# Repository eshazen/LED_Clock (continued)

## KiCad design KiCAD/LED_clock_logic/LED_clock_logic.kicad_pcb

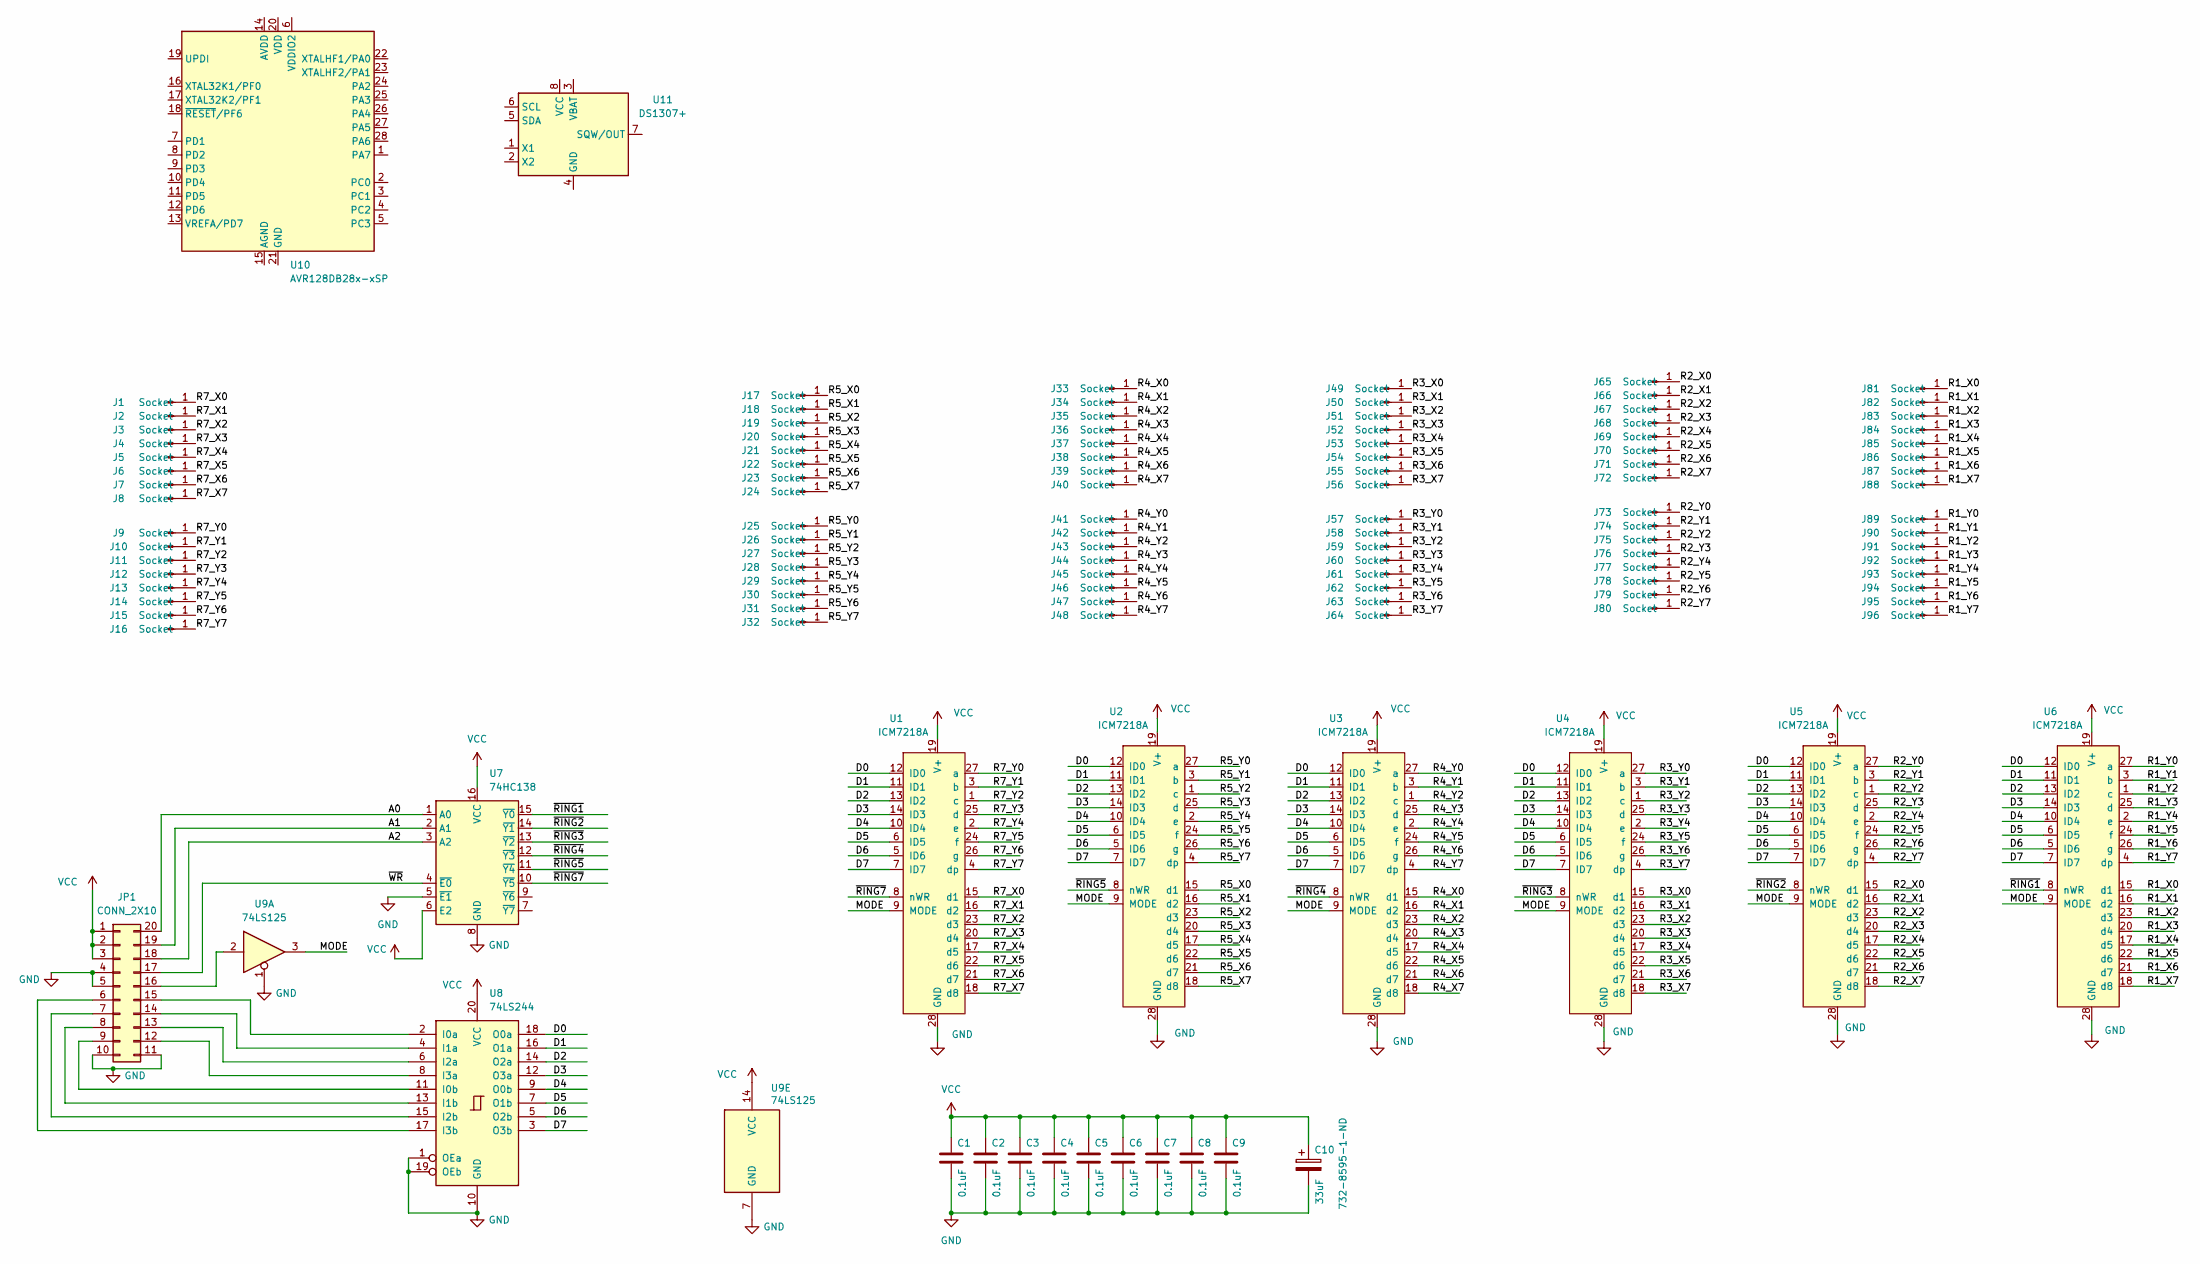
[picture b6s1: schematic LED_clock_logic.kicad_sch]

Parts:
C1, C2, C3, C4, C5, C6, C7, C8, C9: 0.1uF; C_Disc_D4.3mm_W1.9mm_P5.00mm
C10: 33uF; CP_Radial_D5.0mm_P2.00mm
J1, J2, J3, J4, J5, J6, J7, J8, J9, J10, J11, J12, J13, J14, J15, J16, J17, J18, J19, J20, J21, J22, J23, J24, J25, J26, J27, J28, J29, J30, J31, J32, J33, J34, J35, J36, J37, J38, J39, J40, J41, J42, J43, J44, J45, J46, J47, J48, J49, J50, J51, J52, J53, J54, J55, J56, J57, J58, J59, J60, J61, J62, J63, J64, J65, J66, J67, J68, J69, J70, J71, J72, J73, J74, J75, J76, J77, J78, J79, J80, J81, J82, J83, J84, J85, J86, J87, J88, J89, J90, J91, J92, J93, J94, J95, J96: Socket; TestPoint_THTPad_D2.0mm_Drill1.0mm
JP1: CONN_2X10; PinHeader_2x10_P2.54mm_Vertical
U1, U2, U3, U4, U5, U6: ICM7218A; DIP-28_W15.24mm_LongPads
U7: 74HC138; DIP-16_W7.62mm_LongPads
U8: 74LS244; DIP-20_W7.62mm_LongPads
U9: 74LS125; DIP-14_W7.62mm_LongPads
U10: AVR128DB28x-xSP; DIP-28_W7.62mm
U11: DS1307+; DIP-8_W7.62mm

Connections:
/A0: JP1.20, U7.1 (A0)
/A1: JP1.19, U7.2 (A1)
/A2: JP1.18, U7.3 (A2)
/D0: U1.12 (ID0), U2.12 (ID0), U3.12 (ID0), U4.12 (ID0), U5.12 (ID0), U6.12 (ID0), U8.18 (O0a)
/D1: U1.11 (ID1), U2.11 (ID1), U3.11 (ID1), U4.11 (ID1), U5.11 (ID1), U6.11 (ID1), U8.16 (O1a)
/D2: U1.13 (ID2), U2.13 (ID2), U3.13 (ID2), U4.13 (ID2), U5.13 (ID2), U6.13 (ID2), U8.14 (O2a)
/D3: U1.14 (ID3), U2.14 (ID3), U3.14 (ID3), U4.14 (ID3), U5.14 (ID3), U6.14 (ID3), U8.12 (O3a)
/D4: U1.10 (ID4), U2.10 (ID4), U3.10 (ID4), U4.10 (ID4), U5.10 (ID4), U6.10 (ID4), U8.9 (O0b)
/D5: U1.6 (ID5), U2.6 (ID5), U3.6 (ID5), U4.6 (ID5), U5.6 (ID5), U6.6 (ID5), U8.7 (O1b)
/D6: U1.5 (ID6), U2.5 (ID6), U3.5 (ID6), U4.5 (ID6), U5.5 (ID6), U6.5 (ID6), U8.5 (O2b)
/D7: U1.7 (ID7), U2.7 (ID7), U3.7 (ID7), U4.7 (ID7), U5.7 (ID7), U6.7 (ID7), U8.3 (O3b)
/MODE: U1.9 (MODE), U2.9 (MODE), U3.9 (MODE), U4.9 (MODE), U5.9 (MODE), U6.9 (MODE), U9.3
/R1_X0: J81.1, U6.15 (d1)
/R1_X1: J82.1, U6.16 (d2)
/R1_X2: J83.1, U6.23 (d3)
/R1_X3: J84.1, U6.20 (d4)
/R1_X4: J85.1, U6.17 (d5)
/R1_X5: J86.1, U6.22 (d6)
/R1_X6: J87.1, U6.21 (d7)
/R1_X7: J88.1, U6.18 (d8)
/R1_Y0: J89.1, U6.27 (a)
/R1_Y1: J90.1, U6.3 (b)
/R1_Y2: J91.1, U6.1 (c)
/R1_Y3: J92.1, U6.25 (d)
/R1_Y4: J93.1, U6.2 (e)
/R1_Y5: J94.1, U6.24 (f)
/R1_Y6: J95.1, U6.26 (g)
/R1_Y7: J96.1, U6.4 (dp)
/R2_X0: J65.1, U5.15 (d1)
/R2_X1: J66.1, U5.16 (d2)
/R2_X2: J67.1, U5.23 (d3)
/R2_X3: J68.1, U5.20 (d4)
/R2_X4: J69.1, U5.17 (d5)
/R2_X5: J70.1, U5.22 (d6)
/R2_X6: J71.1, U5.21 (d7)
/R2_X7: J72.1, U5.18 (d8)
/R2_Y0: J73.1, U5.27 (a)
/R2_Y1: J74.1, U5.3 (b)
/R2_Y2: J75.1, U5.1 (c)
/R2_Y3: J76.1, U5.25 (d)
/R2_Y4: J77.1, U5.2 (e)
/R2_Y5: J78.1, U5.24 (f)
/R2_Y6: J79.1, U5.26 (g)
/R2_Y7: J80.1, U5.4 (dp)
/R3_X0: J49.1, U4.15 (d1)
/R3_X1: J50.1, U4.16 (d2)
/R3_X2: J51.1, U4.23 (d3)
/R3_X3: J52.1, U4.20 (d4)
/R3_X4: J53.1, U4.17 (d5)
/R3_X5: J54.1, U4.22 (d6)
/R3_X6: J55.1, U4.21 (d7)
/R3_X7: J56.1, U4.18 (d8)
/R3_Y0: J57.1, U4.27 (a)
/R3_Y1: J58.1, U4.3 (b)
/R3_Y2: J59.1, U4.1 (c)
/R3_Y3: J60.1, U4.25 (d)
/R3_Y4: J61.1, U4.2 (e)
/R3_Y5: J62.1, U4.24 (f)
/R3_Y6: J63.1, U4.26 (g)
/R3_Y7: J64.1, U4.4 (dp)
/R4_X0: J33.1, U3.15 (d1)
/R4_X1: J34.1, U3.16 (d2)
/R4_X2: J35.1, U3.23 (d3)
/R4_X3: J36.1, U3.20 (d4)
/R4_X4: J37.1, U3.17 (d5)
/R4_X5: J38.1, U3.22 (d6)
/R4_X6: J39.1, U3.21 (d7)
/R4_X7: J40.1, U3.18 (d8)
/R4_Y0: J41.1, U3.27 (a)
/R4_Y1: J42.1, U3.3 (b)
/R4_Y2: J43.1, U3.1 (c)
/R4_Y3: J44.1, U3.25 (d)
/R4_Y4: J45.1, U3.2 (e)
/R4_Y5: J46.1, U3.24 (f)
/R4_Y6: J47.1, U3.26 (g)
/R4_Y7: J48.1, U3.4 (dp)
/R5_X0: J17.1, U2.15 (d1)
/R5_X1: J18.1, U2.16 (d2)
/R5_X2: J19.1, U2.23 (d3)
/R5_X3: J20.1, U2.20 (d4)
/R5_X4: J21.1, U2.17 (d5)
/R5_X5: J22.1, U2.22 (d6)
/R5_X6: J23.1, U2.21 (d7)
/R5_X7: J24.1, U2.18 (d8)
/R5_Y0: J25.1, U2.27 (a)
/R5_Y1: J26.1, U2.3 (b)
/R5_Y2: J27.1, U2.1 (c)
/R5_Y3: J28.1, U2.25 (d)
/R5_Y4: J29.1, U2.2 (e)
/R5_Y5: J30.1, U2.24 (f)
/R5_Y6: J31.1, U2.26 (g)
/R5_Y7: J32.1, U2.4 (dp)
/R7_X0: J1.1, U1.15 (d1)
/R7_X1: J2.1, U1.16 (d2)
/R7_X2: J3.1, U1.23 (d3)
/R7_X3: J4.1, U1.20 (d4)
/R7_X4: J5.1, U1.17 (d5)
/R7_X5: J6.1, U1.22 (d6)
/R7_X6: J7.1, U1.21 (d7)
/R7_X7: J8.1, U1.18 (d8)
/R7_Y0: J9.1, U1.27 (a)
/R7_Y1: J10.1, U1.3 (b)
/R7_Y2: J11.1, U1.1 (c)
/R7_Y3: J12.1, U1.25 (d)
/R7_Y4: J13.1, U1.2 (e)
/R7_Y5: J14.1, U1.24 (f)
/R7_Y6: J15.1, U1.26 (g)
/R7_Y7: J16.1, U1.4 (dp)
/~RING1: U6.8 (nWR), U7.15 (~Y0)
/~RING2: U5.8 (nWR), U7.14 (~Y1)
/~RING3: U4.8 (nWR), U7.13 (~Y2)
/~RING4: U3.8 (nWR), U7.12 (~Y3)
/~RING5: U2.8 (nWR), U7.11 (~Y4)
/~RING7: U1.8 (nWR), U7.10 (~Y5)
/~WR: JP1.17, U7.4 (~E0)
GND: C1.2, C2.2, C3.2, C4.2, C5.2, C6.2, C7.2, C8.2, C9.2, C10.2, JP1.4, JP1.5, JP1.10, JP1.11, U1.28 (GND), U2.28 (GND), U3.28 (GND), U4.28 (GND), U5.28 (GND), U6.28 (GND), U7.5 (~E1), U7.8 (GND), U8.1 (OEa), U8.10 (GND), U8.19 (OEb), U9.1, U9.7 (GND)
unnamed: JP1.6, U8.17 (I3b)
unnamed: JP1.7, U8.15 (I2b)
unnamed: JP1.8, U8.13 (I1b)
unnamed: JP1.9, U8.11 (I0b)
unnamed: JP1.12, U8.8 (I3a)
unnamed: JP1.13, U8.6 (I2a)
unnamed: JP1.14, U8.4 (I1a)
unnamed: JP1.15, U8.2 (I0a)
unnamed: JP1.16, U9.2
VCC: C1.1, C2.1, C3.1, C4.1, C5.1, C6.1, C7.1, C8.1, C9.1, C10.1, JP1.1, JP1.2, JP1.3, U1.19 (V+), U2.19 (V+), U3.19 (V+), U4.19 (V+), U5.19 (V+), U6.19 (V+), U7.6 (E2), U7.16 (VCC), U8.20 (VCC), U9.14 (VCC)

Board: 2 copper layers, 118 parts (0 on the bottom side), 126 nets, no tracks yet.

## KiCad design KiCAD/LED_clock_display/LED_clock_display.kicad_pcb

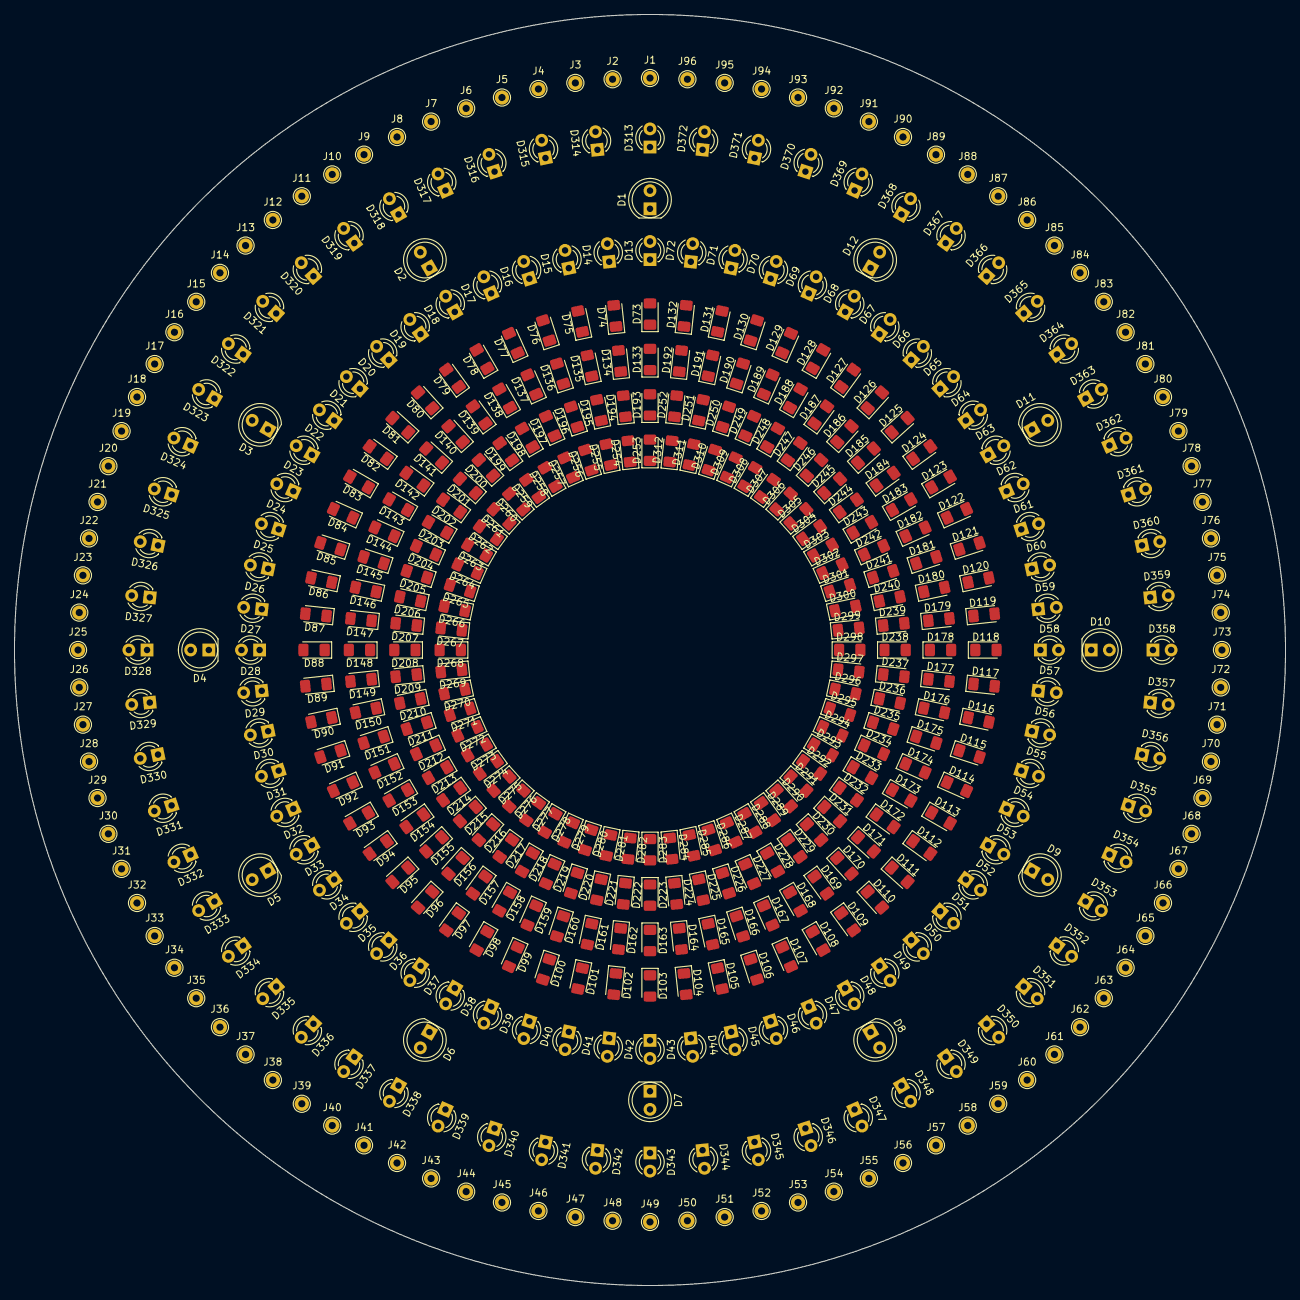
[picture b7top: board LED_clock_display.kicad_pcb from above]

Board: 2 copper layers, 177.8 x 177.8 mm, 468 parts (0 on the bottom side), 96 nets, no tracks yet.

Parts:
D1, D2, D3, D4, D5, D6, D7, D8, D9, D10, D11, D12: LED; LED_D5.0mm
D13, D14, D15, D16, D17, D18, D19, D20, D21, D22, D23, D24, D25, D26, D27, D28, D29, D30, D31, D32, D33, D34, D35, D36, D37, D38, D39, D40, D41, D42, D43, D44, D45, D46, D47, D48, D49, D50, D51, D52, D53, D54, D55, D56, D57, D58, D59, D60, D61, D62, D63, D64, D65, D66, D67, D68, D69, D70, D71, D72, D313, D314, D315, D316, D317, D318, D319, D320, D321, D322, D323, D324, D325, D326, D327, D328, D329, D330, D331, D332, D333, D334, D335, D336, D337, D338, D339, D340, D341, D342, D343, D344, D345, D346, D347, D348, D349, D350, D351, D352, D353, D354, D355, D356, D357, D358, D359, D360, D361, D362, D363, D364, D365, D366, D367, D368, D369, D370, D371, D372: LED; LED_D3.0mm
D73, D74, D75, D76, D77, D78, D79, D80, D81, D82, D83, D84, D85, D86, D87, D88, D89, D90, D91, D92, D93, D94, D95, D96, D97, D98, D99, D100, D101, D102, D103, D104, D105, D106, D107, D108, D109, D110, D111, D112, D113, D114, D115, D116, D117, D118, D119, D120, D121, D122, D123, D124, D125, D126, D127, D128, D129, D130, D131, D132, D133, D134, D135, D136, D137, D138, D139, D140, D141, D142, D143, D144, D145, D146, D147, D148, D149, D150, D151, D152, D153, D154, D155, D156, D157, D158, D159, D160, D161, D162, D163, D164, D165, D166, D167, D168, D169, D170, D171, D172, D173, D174, D175, D176, D177, D178, D179, D180, D181, D182, D183, D184, D185, D186, D187, D188, D189, D190, D191, D192, D193, D194, D195, D196, D197, D198, D199, D200, D201, D202, D203, D204, D205, D206, D207, D208, D209, D210, D211, D212, D213, D214, D215, D216, D217, D218, D219, D220, D221, D222, D223, D224, D225, D226, D227, D228, D229, D230, D231, D232, D233, D234, D235, D236, D237, D238, D239, D240, D241, D242, D243, D244, D245, D246, D247, D248, D249, D250, D251, D252, D253, D254, D255, D256, D257, D258, D259, D260, D261, D262, D263, D264, D265, D266, D267, D268, D269, D270, D271, D272, D273, D274, D275, D276, D277, D278, D279, D280, D281, D282, D283, D284, D285, D286, D287, D288, D289, D290, D291, D292, D293, D294, D295, D296, D297, D298, D299, D300, D301, D302, D303, D304, D305, D306, D307, D308, D309, D310, D311, D312: LED; LED_1206_3216Metric_Pad1.42x1.75mm_HandSolder
J1, J2, J3, J4, J5, J6, J7, J8, J9, J10, J11, J12, J13, J14, J15, J16, J17, J18, J19, J20, J21, J22, J23, J24, J25, J26, J27, J28, J29, J30, J31, J32, J33, J34, J35, J36, J37, J38, J39, J40, J41, J42, J43, J44, J45, J46, J47, J48, J49, J50, J51, J52, J53, J54, J55, J56, J57, J58, J59, J60, J61, J62, J63, J64, J65, J66, J67, J68, J69, J70, J71, J72, J73, J74, J75, J76, J77, J78, J79, J80, J81, J82, J83, J84, J85, J86, J87, J88, J89, J90, J91, J92, J93, J94, J95, J96: PIN; TestPoint_THTPad_D2.0mm_Drill1.0mm

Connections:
/R1_X0: D253.2 (A), D261.2 (A), D269.2 (A), D277.2 (A), D285.2 (A), D293.2 (A), D301.2 (A), D309.2 (A), J81.1
/R1_X1: D254.2 (A), D262.2 (A), D270.2 (A), D278.2 (A), D286.2 (A), D294.2 (A), D302.2 (A), D310.2 (A), J82.1
/R1_X2: D255.2 (A), D263.2 (A), D271.2 (A), D279.2 (A), D287.2 (A), D295.2 (A), D303.2 (A), D311.2 (A), J83.1
/R1_X3: D256.2 (A), D264.2 (A), D272.2 (A), D280.2 (A), D288.2 (A), D296.2 (A), D304.2 (A), D312.2 (A), J84.1
/R1_X4: D257.2 (A), D265.2 (A), D273.2 (A), D281.2 (A), D289.2 (A), D297.2 (A), D305.2 (A), J85.1
/R1_X5: D258.2 (A), D266.2 (A), D274.2 (A), D282.2 (A), D290.2 (A), D298.2 (A), D306.2 (A), J86.1
/R1_X6: D259.2 (A), D267.2 (A), D275.2 (A), D283.2 (A), D291.2 (A), D299.2 (A), D307.2 (A), J87.1
/R1_X7: D260.2 (A), D268.2 (A), D276.2 (A), D284.2 (A), D292.2 (A), D300.2 (A), D308.2 (A), J88.1
/R1_Y0: D253.1 (K), D254.1 (K), D255.1 (K), D256.1 (K), D257.1 (K), D258.1 (K), D259.1 (K), D260.1 (K), J89.1
/R1_Y1: D261.1 (K), D262.1 (K), D263.1 (K), D264.1 (K), D265.1 (K), D266.1 (K), D267.1 (K), D268.1 (K), J90.1
/R1_Y2: D269.1 (K), D270.1 (K), D271.1 (K), D272.1 (K), D273.1 (K), D274.1 (K), D275.1 (K), D276.1 (K), J91.1
/R1_Y3: D277.1 (K), D278.1 (K), D279.1 (K), D280.1 (K), D281.1 (K), D282.1 (K), D283.1 (K), D284.1 (K), J92.1
/R1_Y4: D285.1 (K), D286.1 (K), D287.1 (K), D288.1 (K), D289.1 (K), D290.1 (K), D291.1 (K), D292.1 (K), J93.1
/R1_Y5: D293.1 (K), D294.1 (K), D295.1 (K), D296.1 (K), D297.1 (K), D298.1 (K), D299.1 (K), D300.1 (K), J94.1
/R1_Y6: D301.1 (K), D302.1 (K), D303.1 (K), D304.1 (K), D305.1 (K), D306.1 (K), D307.1 (K), D308.1 (K), J95.1
/R1_Y7: D309.1 (K), D310.1 (K), D311.1 (K), D312.1 (K), J96.1
/R2_X0: D193.2 (A), D201.2 (A), D209.2 (A), D217.2 (A), D225.2 (A), D233.2 (A), D241.2 (A), D249.2 (A), J65.1
/R2_X1: D194.2 (A), D202.2 (A), D210.2 (A), D218.2 (A), D226.2 (A), D234.2 (A), D242.2 (A), D250.2 (A), J66.1
/R2_X2: D195.2 (A), D203.2 (A), D211.2 (A), D219.2 (A), D227.2 (A), D235.2 (A), D243.2 (A), D251.2 (A), J67.1
/R2_X3: D196.2 (A), D204.2 (A), D212.2 (A), D220.2 (A), D228.2 (A), D236.2 (A), D244.2 (A), D252.2 (A), J68.1
/R2_X4: D197.2 (A), D205.2 (A), D213.2 (A), D221.2 (A), D229.2 (A), D237.2 (A), D245.2 (A), J69.1
/R2_X5: D198.2 (A), D206.2 (A), D214.2 (A), D222.2 (A), D230.2 (A), D238.2 (A), D246.2 (A), J70.1
/R2_X6: D199.2 (A), D207.2 (A), D215.2 (A), D223.2 (A), D231.2 (A), D239.2 (A), D247.2 (A), J71.1
/R2_X7: D200.2 (A), D208.2 (A), D216.2 (A), D224.2 (A), D232.2 (A), D240.2 (A), D248.2 (A), J72.1
/R2_Y0: D193.1 (K), D194.1 (K), D195.1 (K), D196.1 (K), D197.1 (K), D198.1 (K), D199.1 (K), D200.1 (K), J73.1
/R2_Y1: D201.1 (K), D202.1 (K), D203.1 (K), D204.1 (K), D205.1 (K), D206.1 (K), D207.1 (K), D208.1 (K), J74.1
/R2_Y2: D209.1 (K), D210.1 (K), D211.1 (K), D212.1 (K), D213.1 (K), D214.1 (K), D215.1 (K), D216.1 (K), J75.1
/R2_Y3: D217.1 (K), D218.1 (K), D219.1 (K), D220.1 (K), D221.1 (K), D222.1 (K), D223.1 (K), D224.1 (K), J76.1
/R2_Y4: D225.1 (K), D226.1 (K), D227.1 (K), D228.1 (K), D229.1 (K), D230.1 (K), D231.1 (K), D232.1 (K), J77.1
/R2_Y5: D233.1 (K), D234.1 (K), D235.1 (K), D236.1 (K), D237.1 (K), D238.1 (K), D239.1 (K), D240.1 (K), J78.1
/R2_Y6: D241.1 (K), D242.1 (K), D243.1 (K), D244.1 (K), D245.1 (K), D246.1 (K), D247.1 (K), D248.1 (K), J79.1
/R2_Y7: D249.1 (K), D250.1 (K), D251.1 (K), D252.1 (K), J80.1
/R3_X0: D133.2 (A), D141.2 (A), D149.2 (A), D157.2 (A), D165.2 (A), D173.2 (A), D181.2 (A), D189.2 (A), J49.1
/R3_X1: D134.2 (A), D142.2 (A), D150.2 (A), D158.2 (A), D166.2 (A), D174.2 (A), D182.2 (A), D190.2 (A), J50.1
/R3_X2: D135.2 (A), D143.2 (A), D151.2 (A), D159.2 (A), D167.2 (A), D175.2 (A), D183.2 (A), D191.2 (A), J51.1
/R3_X3: D136.2 (A), D144.2 (A), D152.2 (A), D160.2 (A), D168.2 (A), D176.2 (A), D184.2 (A), D192.2 (A), J52.1
/R3_X4: D137.2 (A), D145.2 (A), D153.2 (A), D161.2 (A), D169.2 (A), D177.2 (A), D185.2 (A), J53.1
/R3_X5: D138.2 (A), D146.2 (A), D154.2 (A), D162.2 (A), D170.2 (A), D178.2 (A), D186.2 (A), J54.1
/R3_X6: D139.2 (A), D147.2 (A), D155.2 (A), D163.2 (A), D171.2 (A), D179.2 (A), D187.2 (A), J55.1
/R3_X7: D140.2 (A), D148.2 (A), D156.2 (A), D164.2 (A), D172.2 (A), D180.2 (A), D188.2 (A), J56.1
/R3_Y0: D133.1 (K), D134.1 (K), D135.1 (K), D136.1 (K), D137.1 (K), D138.1 (K), D139.1 (K), D140.1 (K), J57.1
/R3_Y1: D141.1 (K), D142.1 (K), D143.1 (K), D144.1 (K), D145.1 (K), D146.1 (K), D147.1 (K), D148.1 (K), J58.1
/R3_Y2: D149.1 (K), D150.1 (K), D151.1 (K), D152.1 (K), D153.1 (K), D154.1 (K), D155.1 (K), D156.1 (K), J59.1
/R3_Y3: D157.1 (K), D158.1 (K), D159.1 (K), D160.1 (K), D161.1 (K), D162.1 (K), D163.1 (K), D164.1 (K), J60.1
/R3_Y4: D165.1 (K), D166.1 (K), D167.1 (K), D168.1 (K), D169.1 (K), D170.1 (K), D171.1 (K), D172.1 (K), J61.1
/R3_Y5: D173.1 (K), D174.1 (K), D175.1 (K), D176.1 (K), D177.1 (K), D178.1 (K), D179.1 (K), D180.1 (K), J62.1
/R3_Y6: D181.1 (K), D182.1 (K), D183.1 (K), D184.1 (K), D185.1 (K), D186.1 (K), D187.1 (K), D188.1 (K), J63.1
/R3_Y7: D189.1 (K), D190.1 (K), D191.1 (K), D192.1 (K), J64.1
/R4_X0: D73.2 (A), D81.2 (A), D89.2 (A), D97.2 (A), D105.2 (A), D113.2 (A), D121.2 (A), D129.2 (A), J33.1
/R4_X1: D74.2 (A), D82.2 (A), D90.2 (A), D98.2 (A), D106.2 (A), D114.2 (A), D122.2 (A), D130.2 (A), J34.1
/R4_X2: D75.2 (A), D83.2 (A), D91.2 (A), D99.2 (A), D107.2 (A), D115.2 (A), D123.2 (A), D131.2 (A), J35.1
/R4_X3: D76.2 (A), D84.2 (A), D92.2 (A), D100.2 (A), D108.2 (A), D116.2 (A), D124.2 (A), D132.2 (A), J36.1
/R4_X4: D9.1 (K), D77.2 (A), D85.2 (A), D93.2 (A), D101.2 (A), D109.2 (A), D117.2 (A), D125.2 (A), J37.1
/R4_X5: D10.1 (K), D78.2 (A), D86.2 (A), D94.2 (A), D102.2 (A), D110.2 (A), D118.2 (A), D126.2 (A), J38.1
/R4_X6: D11.1 (K), D79.2 (A), D87.2 (A), D95.2 (A), D103.2 (A), D111.2 (A), D119.2 (A), D127.2 (A), J39.1
/R4_X7: D12.1 (K), D80.2 (A), D88.2 (A), D96.2 (A), D104.2 (A), D112.2 (A), D120.2 (A), D128.2 (A), J40.1
/R4_Y0: D73.1 (K), D74.1 (K), D75.1 (K), D76.1 (K), D77.1 (K), D78.1 (K), D79.1 (K), D80.1 (K), J41.1
/R4_Y1: D81.1 (K), D82.1 (K), D83.1 (K), D84.1 (K), D85.1 (K), D86.1 (K), D87.1 (K), D88.1 (K), J42.1
/R4_Y2: D89.1 (K), D90.1 (K), D91.1 (K), D92.1 (K), D93.1 (K), D94.1 (K), D95.1 (K), D96.1 (K), J43.1
/R4_Y3: D97.1 (K), D98.1 (K), D99.1 (K), D100.1 (K), D101.1 (K), D102.1 (K), D103.1 (K), D104.1 (K), J44.1
/R4_Y4: D105.1 (K), D106.1 (K), D107.1 (K), D108.1 (K), D109.1 (K), D110.1 (K), D111.1 (K), D112.1 (K), J45.1
/R4_Y5: D113.1 (K), D114.1 (K), D115.1 (K), D116.1 (K), D117.1 (K), D118.1 (K), D119.1 (K), D120.1 (K), J46.1
/R4_Y6: D9.2 (A), D10.2 (A), D11.2 (A), D12.2 (A), D121.1 (K), D122.1 (K), D123.1 (K), D124.1 (K), D125.1 (K), D126.1 (K), D127.1 (K), D128.1 (K), J47.1
/R4_Y7: D129.1 (K), D130.1 (K), D131.1 (K), D132.1 (K), J48.1
/R5_X0: D13.2 (A), D21.2 (A), D29.2 (A), D37.2 (A), D45.2 (A), D53.2 (A), D61.2 (A), D69.2 (A), J17.1
/R5_X1: D14.2 (A), D22.2 (A), D30.2 (A), D38.2 (A), D46.2 (A), D54.2 (A), D62.2 (A), D70.2 (A), J18.1
/R5_X2: D15.2 (A), D23.2 (A), D31.2 (A), D39.2 (A), D47.2 (A), D55.2 (A), D63.2 (A), D71.2 (A), J19.1
/R5_X3: D16.2 (A), D24.2 (A), D32.2 (A), D40.2 (A), D48.2 (A), D56.2 (A), D64.2 (A), D72.2 (A), J20.1
/R5_X4: D5.1 (K), D17.2 (A), D25.2 (A), D33.2 (A), D41.2 (A), D49.2 (A), D57.2 (A), D65.2 (A), J21.1
/R5_X5: D6.1 (K), D18.2 (A), D26.2 (A), D34.2 (A), D42.2 (A), D50.2 (A), D58.2 (A), D66.2 (A), J22.1
/R5_X6: D7.1 (K), D19.2 (A), D27.2 (A), D35.2 (A), D43.2 (A), D51.2 (A), D59.2 (A), D67.2 (A), J23.1
/R5_X7: D8.1 (K), D20.2 (A), D28.2 (A), D36.2 (A), D44.2 (A), D52.2 (A), D60.2 (A), D68.2 (A), J24.1
/R5_Y0: D13.1 (K), D14.1 (K), D15.1 (K), D16.1 (K), D17.1 (K), D18.1 (K), D19.1 (K), D20.1 (K), J25.1
/R5_Y1: D21.1 (K), D22.1 (K), D23.1 (K), D24.1 (K), D25.1 (K), D26.1 (K), D27.1 (K), D28.1 (K), J26.1
/R5_Y2: D29.1 (K), D30.1 (K), D31.1 (K), D32.1 (K), D33.1 (K), D34.1 (K), D35.1 (K), D36.1 (K), J27.1
/R5_Y3: D37.1 (K), D38.1 (K), D39.1 (K), D40.1 (K), D41.1 (K), D42.1 (K), D43.1 (K), D44.1 (K), J28.1
/R5_Y4: D45.1 (K), D46.1 (K), D47.1 (K), D48.1 (K), D49.1 (K), D50.1 (K), D51.1 (K), D52.1 (K), J29.1
/R5_Y5: D53.1 (K), D54.1 (K), D55.1 (K), D56.1 (K), D57.1 (K), D58.1 (K), D59.1 (K), D60.1 (K), J30.1
/R5_Y6: D5.2 (A), D6.2 (A), D7.2 (A), D8.2 (A), D61.1 (K), D62.1 (K), D63.1 (K), D64.1 (K), D65.1 (K), D66.1 (K), D67.1 (K), D68.1 (K), J31.1
/R5_Y7: D69.1 (K), D70.1 (K), D71.1 (K), D72.1 (K), J32.1
/R7_X0: D313.2 (A), D321.2 (A), D329.2 (A), D337.2 (A), D345.2 (A), D353.2 (A), D361.2 (A), D369.2 (A), J1.1
/R7_X1: D314.2 (A), D322.2 (A), D330.2 (A), D338.2 (A), D346.2 (A), D354.2 (A), D362.2 (A), D370.2 (A), J2.1
/R7_X2: D315.2 (A), D323.2 (A), D331.2 (A), D339.2 (A), D347.2 (A), D355.2 (A), D363.2 (A), D371.2 (A), J3.1
/R7_X3: D316.2 (A), D324.2 (A), D332.2 (A), D340.2 (A), D348.2 (A), D356.2 (A), D364.2 (A), D372.2 (A), J4.1
/R7_X4: D1.1 (K), D317.2 (A), D325.2 (A), D333.2 (A), D341.2 (A), D349.2 (A), D357.2 (A), D365.2 (A), J5.1
/R7_X5: D2.1 (K), D318.2 (A), D326.2 (A), D334.2 (A), D342.2 (A), D350.2 (A), D358.2 (A), D366.2 (A), J6.1
/R7_X6: D3.1 (K), D319.2 (A), D327.2 (A), D335.2 (A), D343.2 (A), D351.2 (A), D359.2 (A), D367.2 (A), J7.1
/R7_X7: D4.1 (K), D320.2 (A), D328.2 (A), D336.2 (A), D344.2 (A), D352.2 (A), D360.2 (A), D368.2 (A), J8.1
/R7_Y0: D313.1 (K), D314.1 (K), D315.1 (K), D316.1 (K), D317.1 (K), D318.1 (K), D319.1 (K), D320.1 (K), J9.1
/R7_Y1: D321.1 (K), D322.1 (K), D323.1 (K), D324.1 (K), D325.1 (K), D326.1 (K), D327.1 (K), D328.1 (K), J10.1
/R7_Y2: D329.1 (K), D330.1 (K), D331.1 (K), D332.1 (K), D333.1 (K), D334.1 (K), D335.1 (K), D336.1 (K), J11.1
/R7_Y3: D337.1 (K), D338.1 (K), D339.1 (K), D340.1 (K), D341.1 (K), D342.1 (K), D343.1 (K), D344.1 (K), J12.1
/R7_Y4: D345.1 (K), D346.1 (K), D347.1 (K), D348.1 (K), D349.1 (K), D350.1 (K), D351.1 (K), D352.1 (K), J13.1
/R7_Y5: D353.1 (K), D354.1 (K), D355.1 (K), D356.1 (K), D357.1 (K), D358.1 (K), D359.1 (K), D360.1 (K), J14.1
/R7_Y6: D1.2 (A), D2.2 (A), D3.2 (A), D4.2 (A), D361.1 (K), D362.1 (K), D363.1 (K), D364.1 (K), D365.1 (K), D366.1 (K), D367.1 (K), D368.1 (K), J15.1
/R7_Y7: D369.1 (K), D370.1 (K), D371.1 (K), D372.1 (K), J16.1

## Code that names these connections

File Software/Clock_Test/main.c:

/*
 * Simple serial RTC firmware
 *
 * Read time from DS3231 module via I2C and send as [hh:mm:ss]
 * via software uart at 1200 baud on PB0.
 *
 * Set buttons are on PA0..PA2
 * PA0 - set hours
 * PA1 - set minutes
 * PA2 - reset seconds to 00
 */

#include <avr/io.h>
#include <util/delay.h>

#include "ds3231.h"
#include "uart_tx.h"
#include "u8_str.h"

uint8_t sec, min, hour, day, date, month, year;

char buff[10];

void send_time() {
    ds3231_get_time(&sec, &min, &hour, &day, &date, &month, &year);
    uart_tx_byte( '[');
    u8_to_str2( hour, buff);
    uart_tx_string( buff);
    uart_tx_byte( ':');
    u8_to_str2( min, buff);
    uart_tx_string( buff);
    uart_tx_byte( ':');
    u8_to_str2( sec, buff);
    uart_tx_string( buff);
    uart_tx_byte( ']');
    uart_tx_string("\r\n");
}

// button scan delay
#define SCAN_MS 200

// number of scan periods between clock updates (1 min per update)
// #define UPDATE_TICKS (60000L/SCAN_MS)
#define UPDATE_TICKS 50

int main() {

  uint8_t b_set, tick, send_delay;

  uart_init();
  PORTA |= 7;			/* pull-ups on PA0..PA2 (buttons) */

  tick = 0;
  send_delay = 0;

  while(1) {
    // check for set buttons
    b_set = (PINA & 7) ^ 7;

    if( b_set) {		/* any set buttons pressed? */
      ds3231_get_time(&sec, &min, &hour, &day, &date, &month, &year);

      if( b_set & 1) {		/* hour set */
	hour++;
	if( hour > 23)
	  hour -= 24;
      }

      if( b_set & 2) {		/* min set */
	min++;
	if( min > 59)
	  min = 0;
      }

      if( b_set & 4) {		/* sec set */
	sec = 0;
      }
      ds3231_set_time(sec, min, hour, day, date, month, year);
      send_time();
    }

    _delay_ms(SCAN_MS);		/* check buttons at 5Hz */

    ++tick;
    if( tick >= UPDATE_TICKS) {
      tick = 0;
      send_time();
    }
  }
}

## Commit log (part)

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2026-01-19 Starting on PCB
2026-01-20 initial placement
2026-01-20 Split into two boards
2026-01-20 adding Z80
2026-01-21 tentative placement
2026-01-21 paused placement
2026-01-21 working on sector-ized layout
2026-01-21 Sector-based layout
2026-01-22 rev 1?
2026-01-22 create proto sector
2026-01-23 prototype sector
2026-01-23 rearrange folders to purge history
2026-02-04 mounting clip
2026-02-13 README
2026-02-18 control panel start
2026-02-22 first test on pcb
2026-02-23 sector test
2026-02-24 test software for full build
2026-02-24 work on control panel
2026-02-24 first (untested) time display
2026-02-24 MiniRTC board
2026-02-24 add buttons to simple RTC, change to ATTiny84
2026-02-25 NTP version working
2026-02-25 Mounting plate with buttons
2026-02-26 hangar
2026-02-27 update SW
2026-03-01 Clean up a bit
2026-03-01 update the code
2026-03-01 tweak code to reset seconds on 00 on minute set
2026-03-01 Fix? the clock code
2026-03-26 As built SimpleRTC design
2026-04-09 modifying layout for V2
2026-04-12 initial software for RTC
2026-04-19 first v3
2026-04-19 update clock_v3
2026-04-19 first release working
2026-04-19 clock_v3 seems to work with new RTC
2026-04-19 Updated mounting plate
2026-04-20 update setting firmware
2026-04-20 Update the mounting plate
